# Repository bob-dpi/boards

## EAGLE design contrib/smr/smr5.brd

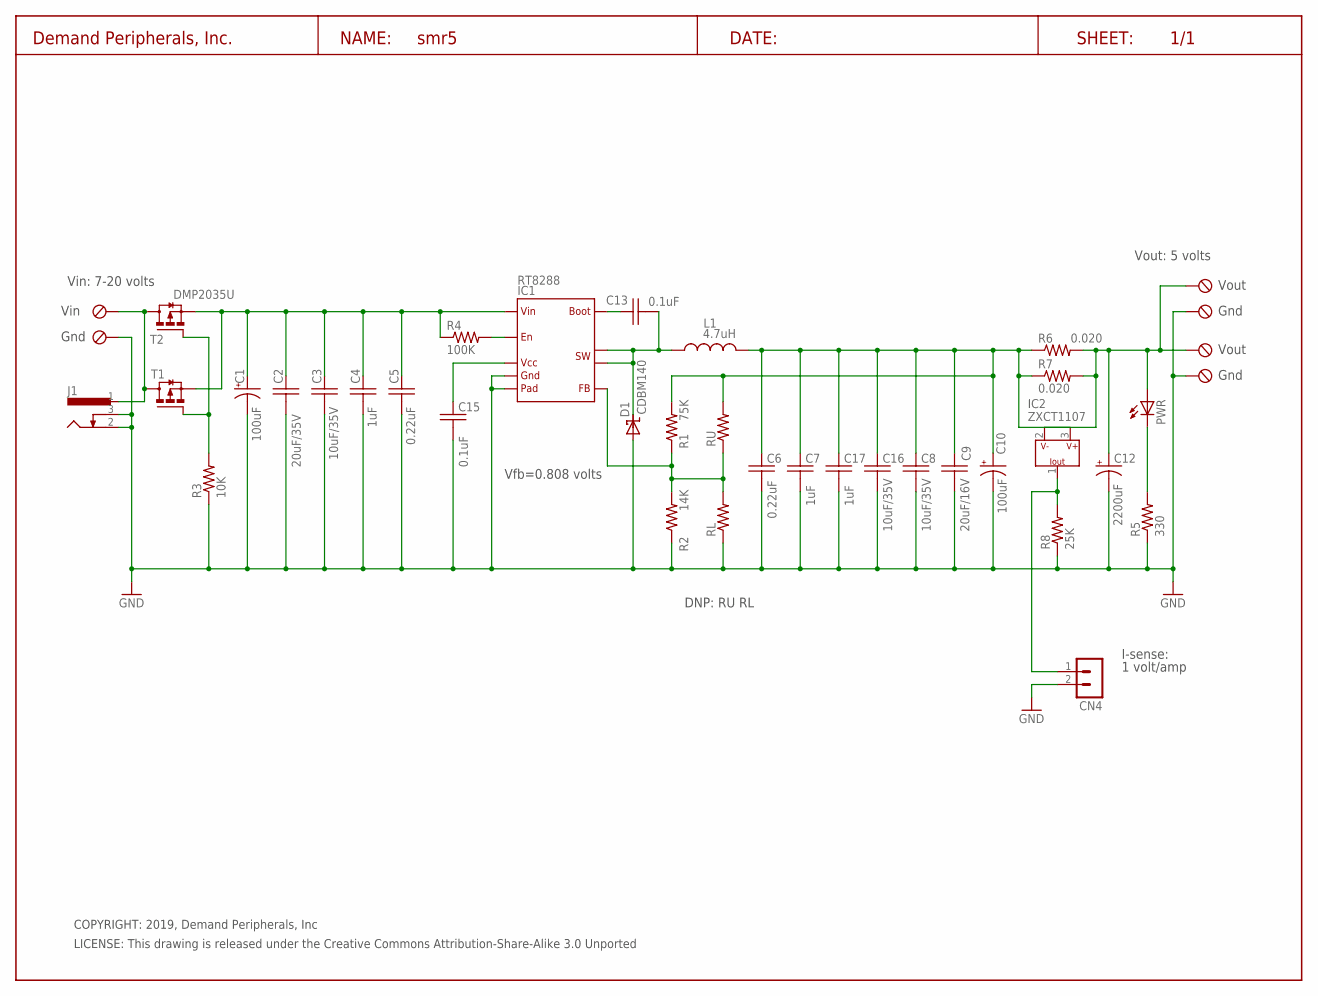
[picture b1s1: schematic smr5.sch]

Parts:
C1, C10: 100uF; E3.5-8
C2: 20uF/35V; C1206
C3, C8, C16: 10uF/35V; C0805
C4, C7, C17: 1uF; C0603
C5, C6: 0.22uF; C0805
C9: 20uF/16V; C1210
C12: 2200uF; E7,5-16
C13, C15: 0.1uF; C0603
CN1, CN2, CN3: TBLK-5.08-X2
CN4: HDR-2X1-LCK; HDR-2X1
D1: CDBM140; SOD123T
IC1: RT8288; SOIC8-PAD
IC2: ZXCT1107; ZXCT
J1: DC-BARREL-JACK--55MM; DC-BARREL-JACK-55MM
L1: 4.7uH; TDKVLFIND
PWR: LED-5MM-RED; LED5MM
R1: 75K; R0603
R2: 14K; R0603
R3: 10K; R0603
R4: 100K; R0603
R5: 330; R0603
R6, R7: 0.020; R0805
R8: 25K; R0603
RL: R0.02_R0805; R0805
RU: R0.02_R0805; R0805
T1, T2: DMP2035U; SOT23
U$1: DP_FRAME_L; LETTER_L

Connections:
GND: C1.-, C2.2, C3.2, C4.2, C5.2, C6.2, C7.2, C8.2, C9.2, C10.-, C12.-, C15.2, C16.2, C17.2, CN1.1 (KL), CN2.1 (KL), CN3.1 (KL), CN4.2 (1), D1.A, IC1.8 (GND), IC1.9 (GND-PAD), J1.2, J1.3, R2.1, R3.1, R5.1, R8.1, RL.1
unnamed: R3.2, T1.1 (G), T2.1 (G)
unnamed: C13.1, IC1.4 (BOOT)
unnamed: C13.2, D1.C (CC), IC1.2 (SW0), IC1.3 (SW1), L1.P$1 (1)
unnamed: PWR.C, R5.2
unnamed: CN4.1 (2), IC2.1 (IOUT), R8.2
unnamed: C12.+, CN2.2 (KL1), CN3.2 (KL1), IC2.2 (V-), PWR.A, R6.2, R7.2
unnamed: IC1.5 (EN), R4.2
unnamed: C15.1, IC1.7 (VCC)
unnamed: IC1.6 (FB), R1.1, R2.2, RL.2, RU.1
unnamed: CN1.2 (KL1), J1.1, T1.3 (D), T2.3 (D)
SW-OUT: C6.1, C7.1, C8.1, C9.1, C10.+, C16.1, C17.1, IC2.3 (V+), L1.P$2 (2), R1.2, R6.1, R7.1, RU.2
V+: C1.+, C2.1, C3.1, C4.1, C5.1, IC1.1 (VIN), R4.1, T1.2 (S), T2.2 (S)

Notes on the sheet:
Gnd
Vout
Vin
COPYRIGHT: 2019, Demand Peripherals, Inc
LICENSE: This drawing is released under the Creative Commons Attribution-Share-Alike 3.0 Unported
Vin: 7-20 volts
Vout: 5 volts
DNP: RU RL
Vfb=0.808 volts
I-sense:
1 volt/amp

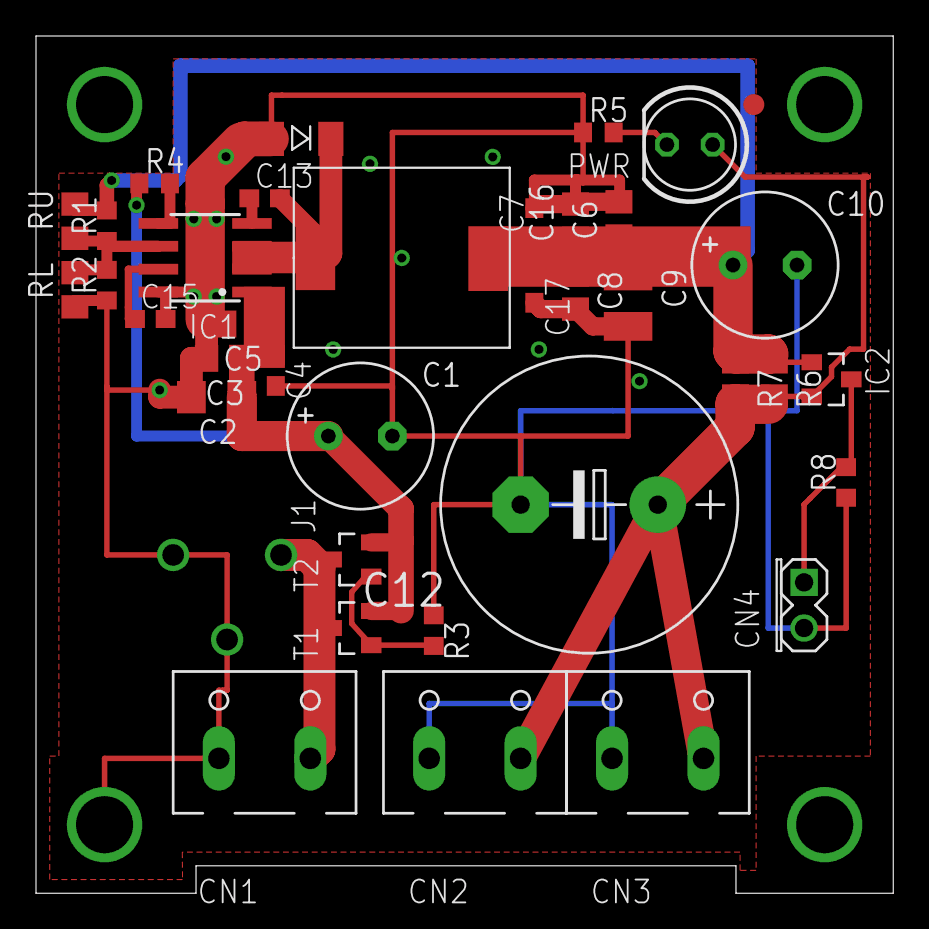
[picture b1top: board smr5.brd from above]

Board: 2 copper layers, 47.6 x 47.6 mm, 40 parts (1 on the bottom side), 13 nets.

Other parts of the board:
U$2: DPI-2
U$3: FIDUCIAL

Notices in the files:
contrib/smr/smr5.brd:
(C) 2019, Demand Peripherals, Inc.
